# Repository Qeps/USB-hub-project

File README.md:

# PCB Design
Four-layer PCB project expanding two USB ports from a computer into eight downstream ports.
Designed in KiCad, conceptually based on the CircuitDigest (Original project: https://circuitdigest.com/electronic-circuits/diy-hub-port-extender) project, but extended to support two independent USB hub controllers.

Base Project (CircuitDigest)
- Uses the GL850G USB 2.0 hub controller
- Expands one USB port into four downstream ports
- Powered directly from 5 V USB input
- The controller integrates internal 3.3 V and 1.8 V regulators, no external LDO required
- Basic passive components: resistors and decoupling capacitors
- USB-A connectors for downstream ports and one upstream connector
- Includes ESD protection (TVS diodes) for both upstream and downstream ports

Extended Version (this project)
- Two upstream USB inputs expanded to eight downstream ports (two hub controllers)
- Implemented on a 4-layer PCB for improved power and signal routing
- Thickened power traces for stable 5 V distribution across all ports
- Matched USB data line lengths to maintain signal integrity and timing
- Guard ring added around USB signal area to improve EMI and ESD immunity
- Independent hub sections sharing common 5 V supply and ground planes

KiCAD schematic:

KiCAD 3D board view:

# Prototype Board
This project is currently under development and PCBWay provided the prototype boards as part of a collaboration. The PCBs arrived with consistent manufacturing quality: clean routing, correct layer alignment, and accurate silkscreen. 

The ordering workflow was straightforward. Uploading the Gerber files and selecting the manufacturing parameters was clear enough that the whole process stayed focused on the technical aspects of the design.

Photo of the prototypes:

Having the boards early in the process accelerates testing and helps refine the next revision.
Here you can order your board: https://www.pcbway.com/

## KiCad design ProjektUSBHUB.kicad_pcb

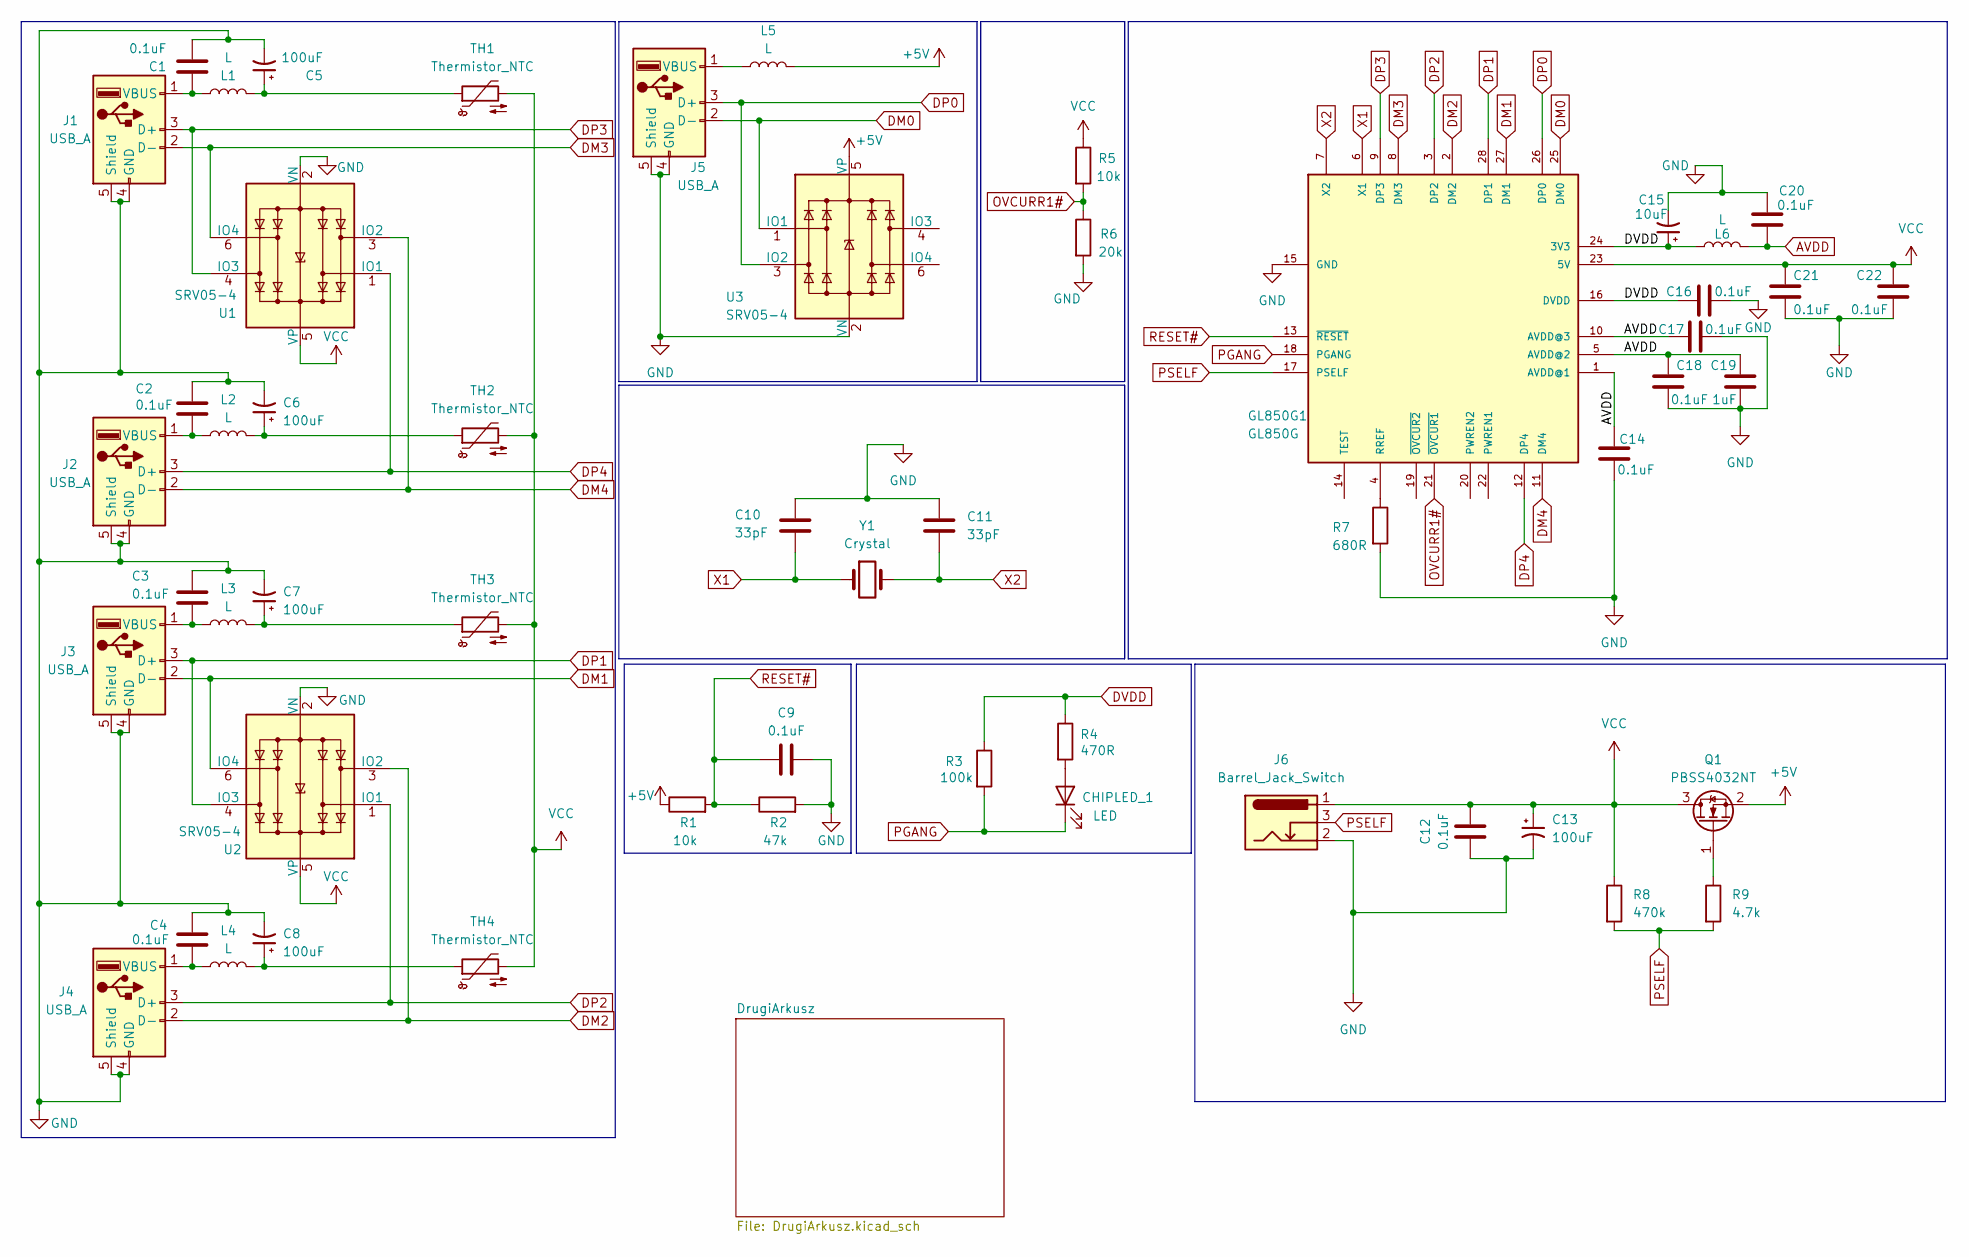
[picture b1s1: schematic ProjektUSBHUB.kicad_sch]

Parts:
C1, C2, C3, C4, C9, C12, C14, C16, C17, C18, C20, C21, C22: 0.1uF; C_0603_1608Metric_Pad1.08x0.95mm_HandSolder
C5, C6, C7, C8, C13: 100uF; C_Radial_D6.3mm_H11.0mm_P2.50mm
C10, C11: 33pF; C_0603_1608Metric_Pad1.08x0.95mm_HandSolder
C15: 10uF; C_Radial_D6.3mm_H11.0mm_P2.50mm
C19: 1uF; C_0603_1608Metric_Pad1.08x0.95mm_HandSolder
CHIPLED_1: LED; D_0805_2012Metric_Pad1.15x1.40mm_HandSolder
GL850G1: GL850G; SSOP28_GL850G_GEN-L
J1, J2, J3, J4, J5: USB_A; USB_A_TE_292303-7_Horizontal
J6: Barrel_Jack_Switch; PJ-102AH
L1, L2, L3, L4, L5, L6: L; L_0603_1608Metric_Pad1.05x0.95mm_HandSolder
Q1: PBSS4032NT; SOT-23
R1, R5: 10k; R_0603_1608Metric_Pad0.98x0.95mm_HandSolder
R2: 47k; R_0603_1608Metric_Pad0.98x0.95mm_HandSolder
R3: 100k; R_0603_1608Metric_Pad0.98x0.95mm_HandSolder
R4: 470R; R_0603_1608Metric_Pad0.98x0.95mm_HandSolder
R6: 20k; R_0603_1608Metric_Pad0.98x0.95mm_HandSolder
R7: 680R; R_0603_1608Metric_Pad0.98x0.95mm_HandSolder
R8: 470k; R_0603_1608Metric_Pad0.98x0.95mm_HandSolder
R9: 4.7k; R_0603_1608Metric_Pad0.98x0.95mm_HandSolder
TH1, TH2, TH3, TH4: Thermistor_NTC; R_0805_2012Metric_Pad1.20x1.40mm_HandSolder
U1, U2, U3: SRV05-4; TSOT-23-6_HandSoldering
Y1: Crystal; Crystal_SMD_ECS_CSM3X-2Pin_7.6x4.1mm

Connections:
+5V: L5.2, Q1.2 (S), R1.1, U3.5 (VP); also elsewhere on the board
AVDD: C14.1, C17.1, C18.1, C19.1, C20.2, GL850G1.1 (AVDD@1), GL850G1.5 (AVDD@2), GL850G1.10 (AVDD@3), L6.2
DM0: GL850G1.25 (DM0), J5.2 (D-), U3.1 (IO1)
DM1: GL850G1.27 (DM1), J3.2 (D-), U2.6 (IO4)
DM2: GL850G1.2 (DM2), J4.2 (D-), U2.3 (IO2)
DM3: GL850G1.8 (DM3), J1.2 (D-), U1.6 (IO4)
DM4: GL850G1.11 (DM4), J2.2 (D-), U1.3 (IO2)
DP0: GL850G1.26 (DP0), J5.3 (D+), U3.3 (IO2)
DP1: GL850G1.28 (DP1), J3.3 (D+), U2.4 (IO3)
DP2: GL850G1.3 (DP2), J4.3 (D+), U2.1 (IO1)
DP3: GL850G1.9 (DP3), J1.3 (D+), U1.4 (IO3)
DP4: GL850G1.12 (DP4), J2.3 (D+), U1.1 (IO1)
DVDD: C15.1, C16.1, GL850G1.16 (DVDD), GL850G1.24 (3V3), L6.1, R3.1, R4.1
GND: C1.2, C2.1, C3.1, C4.1, C5.2, C6.2, C7.2, C8.2, C9.2, C10.1, C11.1, C12.1, C13.2, C14.2, C15.2, C16.2, C17.2, C18.2, C19.2, C20.1, C21.2, C22.2, GL850G1.15 (GND), J1.4 (GND), J1.5 (Shield), J2.4 (GND), J2.5 (Shield), J3.4 (GND), J3.5 (Shield), J4.4 (GND), J4.5 (Shield), J5.4 (GND), J5.5 (Shield), J6.2, R2.2, R6.2, R7.2, U1.2 (VN), U2.2 (VN), U3.2 (VN); also elsewhere on the board
unnamed: C5.1, L1.2, TH1.1
unnamed: C6.1, L2.2, TH2.1
unnamed: C7.1, L3.2, TH3.1
unnamed: C8.1, L4.2, TH4.1
unnamed: CHIPLED_1.2 (A), R4.2
unnamed: GL850G1.4 (RREF), R7.1
unnamed: C1.1, J1.1 (VBUS), L1.1
unnamed: C2.2, J2.1 (VBUS), L2.1
unnamed: C3.2, J3.1 (VBUS), L3.1
unnamed: C4.2, J4.1 (VBUS), L4.1
unnamed: J5.1 (VBUS), L5.1
unnamed: Q1.1 (G), R9.1
OVCURR1#: GL850G1.21 (~OVCUR1), R5.2, R6.1
PGANG: CHIPLED_1.1 (K), GL850G1.18 (PGANG), R3.2
PSELF: GL850G1.17 (PSELF), J6.3, R8.2, R9.2; also elsewhere on the board
RESET#: C9.1, GL850G1.13 (~RESET), R1.2, R2.1
VCC: C12.2, C13.1, C21.1, C22.1, GL850G1.23 (5V), J6.1, Q1.3 (D), R5.1, R8.1, TH1.2, TH2.2, TH3.2, TH4.2, U1.5 (VP), U2.5 (VP); also elsewhere on the board
X1: C10.2, GL850G1.6 (X1), Y1.1
X2: C11.2, GL850G1.7 (X2), Y1.2

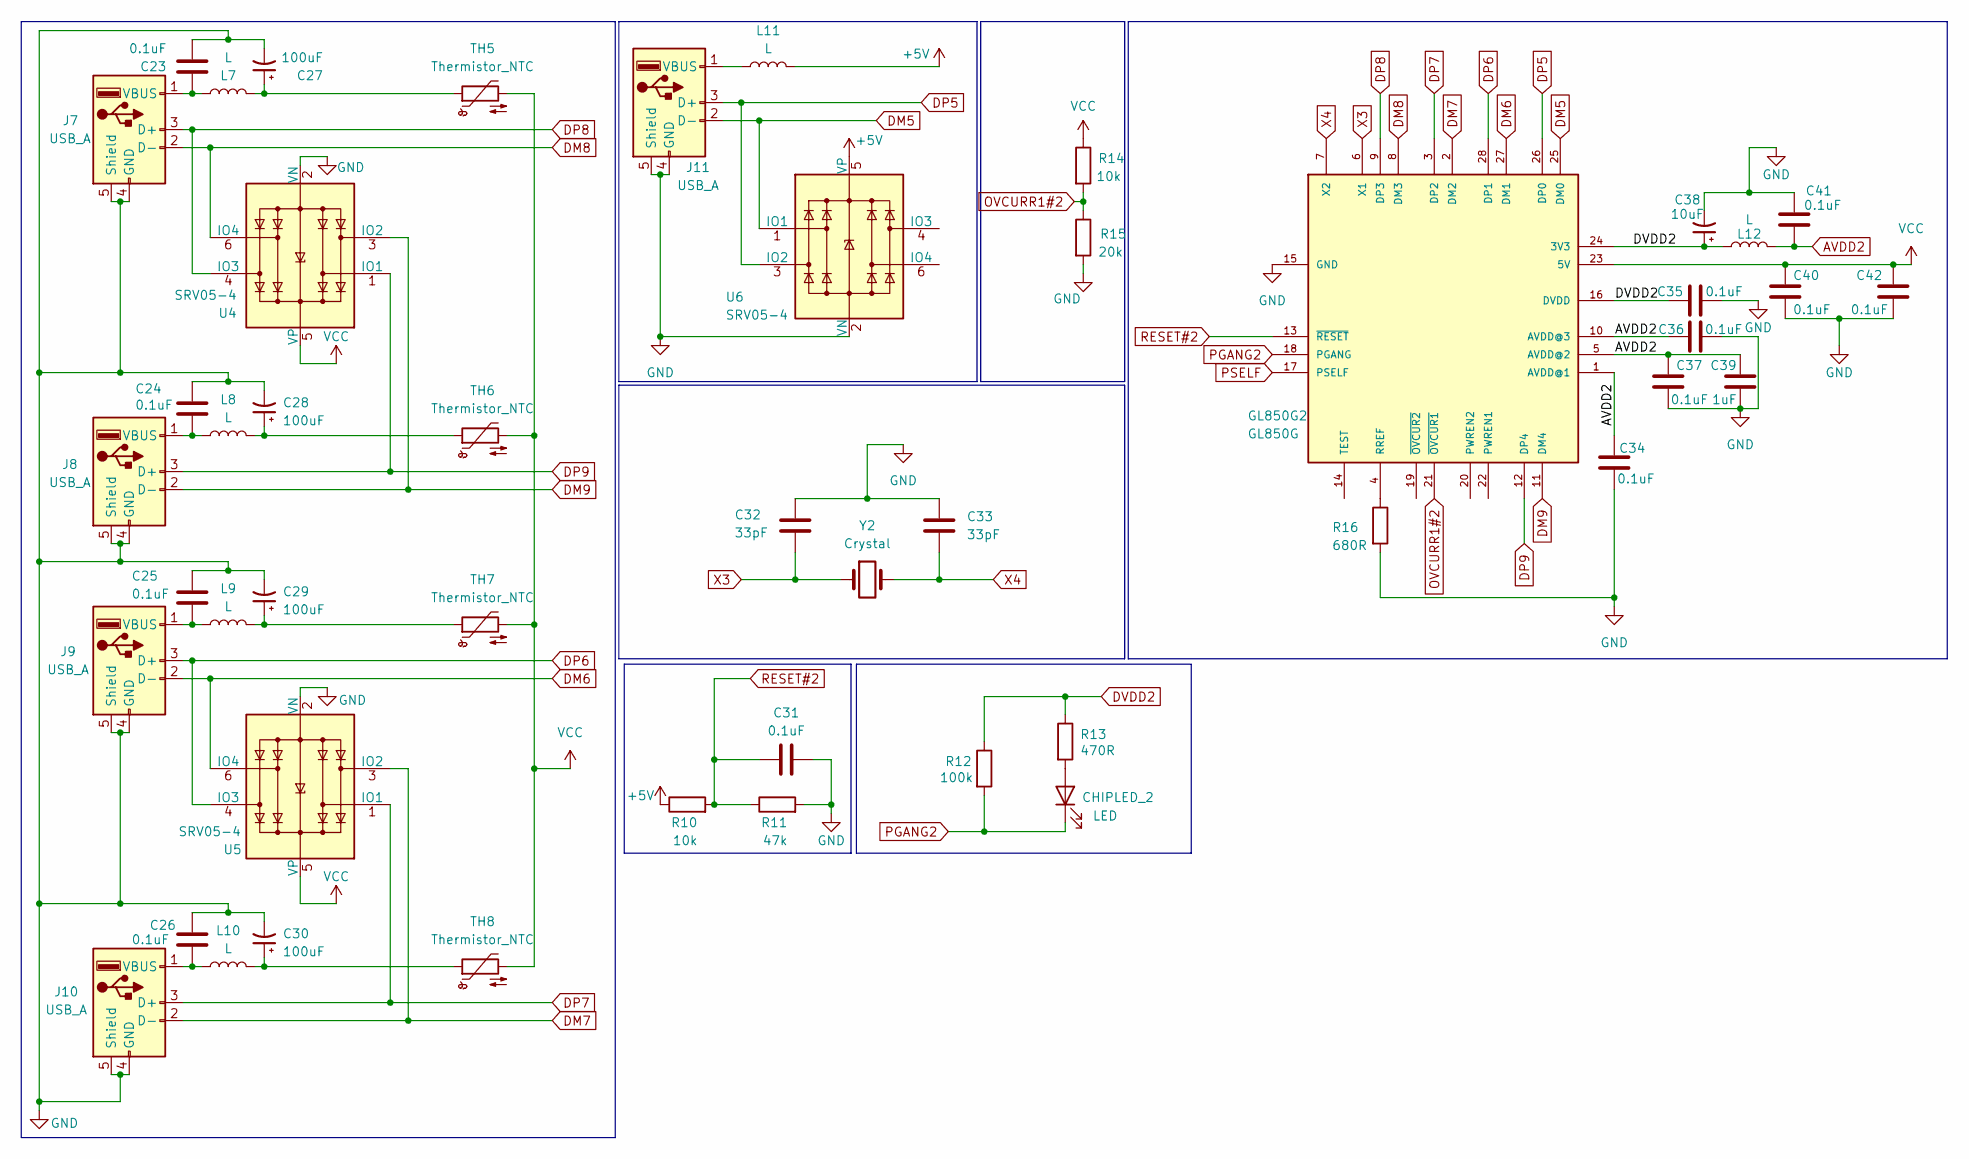
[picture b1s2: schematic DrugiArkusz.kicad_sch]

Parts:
C23, C24, C25, C26, C31, C34, C35, C36, C37, C40, C41, C42: 0.1uF; C_0603_1608Metric_Pad1.08x0.95mm_HandSolder
C27, C28, C29, C30: 100uF; C_Radial_D6.3mm_H11.0mm_P2.50mm
C32, C33: 33pF; C_0603_1608Metric_Pad1.08x0.95mm_HandSolder
C38: 10uF; C_Radial_D6.3mm_H11.0mm_P2.50mm
C39: 1uF; C_0603_1608Metric_Pad1.08x0.95mm_HandSolder
CHIPLED_2: LED; D_0805_2012Metric_Pad1.15x1.40mm_HandSolder
GL850G2: GL850G; SSOP28_GL850G_GEN-L
J7, J8, J9, J10, J11: USB_A; USB_A_TE_292303-7_Horizontal
L7, L8, L9, L10, L11, L12: L; L_0603_1608Metric_Pad1.05x0.95mm_HandSolder
R10, R14: 10k; R_0603_1608Metric_Pad0.98x0.95mm_HandSolder
R11: 47k; R_0603_1608Metric_Pad0.98x0.95mm_HandSolder
R12: 100k; R_0603_1608Metric_Pad0.98x0.95mm_HandSolder
R13: 470R; R_0603_1608Metric_Pad0.98x0.95mm_HandSolder
R15: 20k; R_0603_1608Metric_Pad0.98x0.95mm_HandSolder
R16: 680R; R_0603_1608Metric_Pad0.98x0.95mm_HandSolder
TH5, TH6, TH7, TH8: Thermistor_NTC; R_0805_2012Metric_Pad1.20x1.40mm_HandSolder
U4, U5, U6: SRV05-4; TSOT-23-6_HandSoldering
Y2: Crystal; Crystal_SMD_ECS_CSM3X-2Pin_7.6x4.1mm

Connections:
+5V: L11.2, R10.1, U6.5 (VP); also elsewhere on the board
AVDD2: C34.1, C36.1, C37.1, C39.1, C41.2, GL850G2.1 (AVDD@1), GL850G2.5 (AVDD@2), GL850G2.10 (AVDD@3), L12.2
DM5: GL850G2.25 (DM0), J11.2 (D-), U6.1 (IO1)
DM6: GL850G2.27 (DM1), J9.2 (D-), U5.6 (IO4)
DM7: GL850G2.2 (DM2), J10.2 (D-), U5.3 (IO2)
DM8: GL850G2.8 (DM3), J7.2 (D-), U4.6 (IO4)
DM9: GL850G2.11 (DM4), J8.2 (D-), U4.3 (IO2)
DP5: GL850G2.26 (DP0), J11.3 (D+), U6.3 (IO2)
DP6: GL850G2.28 (DP1), J9.3 (D+), U5.4 (IO3)
DP7: GL850G2.3 (DP2), J10.3 (D+), U5.1 (IO1)
DP8: GL850G2.9 (DP3), J7.3 (D+), U4.4 (IO3)
DP9: GL850G2.12 (DP4), J8.3 (D+), U4.1 (IO1)
DVDD2: C35.1, C38.1, GL850G2.16 (DVDD), GL850G2.24 (3V3), L12.1, R12.1, R13.1
GND: C23.2, C24.1, C25.1, C26.1, C27.2, C28.2, C29.2, C30.2, C31.2, C32.1, C33.1, C34.2, C35.2, C36.2, C37.2, C38.2, C39.2, C40.2, C41.1, C42.2, GL850G2.15 (GND), J7.4 (GND), J7.5 (Shield), J8.4 (GND), J8.5 (Shield), J9.4 (GND), J9.5 (Shield), J10.4 (GND), J10.5 (Shield), J11.4 (GND), J11.5 (Shield), R11.2, R15.2, R16.2, U4.2 (VN), U5.2 (VN), U6.2 (VN); also elsewhere on the board
unnamed: C27.1, L7.2, TH5.1
unnamed: C28.1, L8.2, TH6.1
unnamed: C29.1, L9.2, TH7.1
unnamed: C30.1, L10.2, TH8.1
unnamed: CHIPLED_2.2 (A), R13.2
unnamed: GL850G2.4 (RREF), R16.1
unnamed: C23.1, J7.1 (VBUS), L7.1
unnamed: C24.2, J8.1 (VBUS), L8.1
unnamed: C25.2, J9.1 (VBUS), L9.1
unnamed: C26.2, J10.1 (VBUS), L10.1
unnamed: J11.1 (VBUS), L11.1
OVCURR1#2: GL850G2.21 (~OVCUR1), R14.2, R15.1
PGANG2: CHIPLED_2.1 (K), GL850G2.18 (PGANG), R12.2
PSELF: GL850G2.17 (PSELF); also elsewhere on the board
RESET#2: C31.1, GL850G2.13 (~RESET), R10.2, R11.1
VCC: C40.1, C42.1, GL850G2.23 (5V), R14.1, TH5.2, TH6.2, TH7.2, TH8.2, U4.5 (VP), U5.5 (VP); also elsewhere on the board
X3: C32.2, GL850G2.6 (X1), Y2.1
X4: C33.2, GL850G2.7 (X2), Y2.2

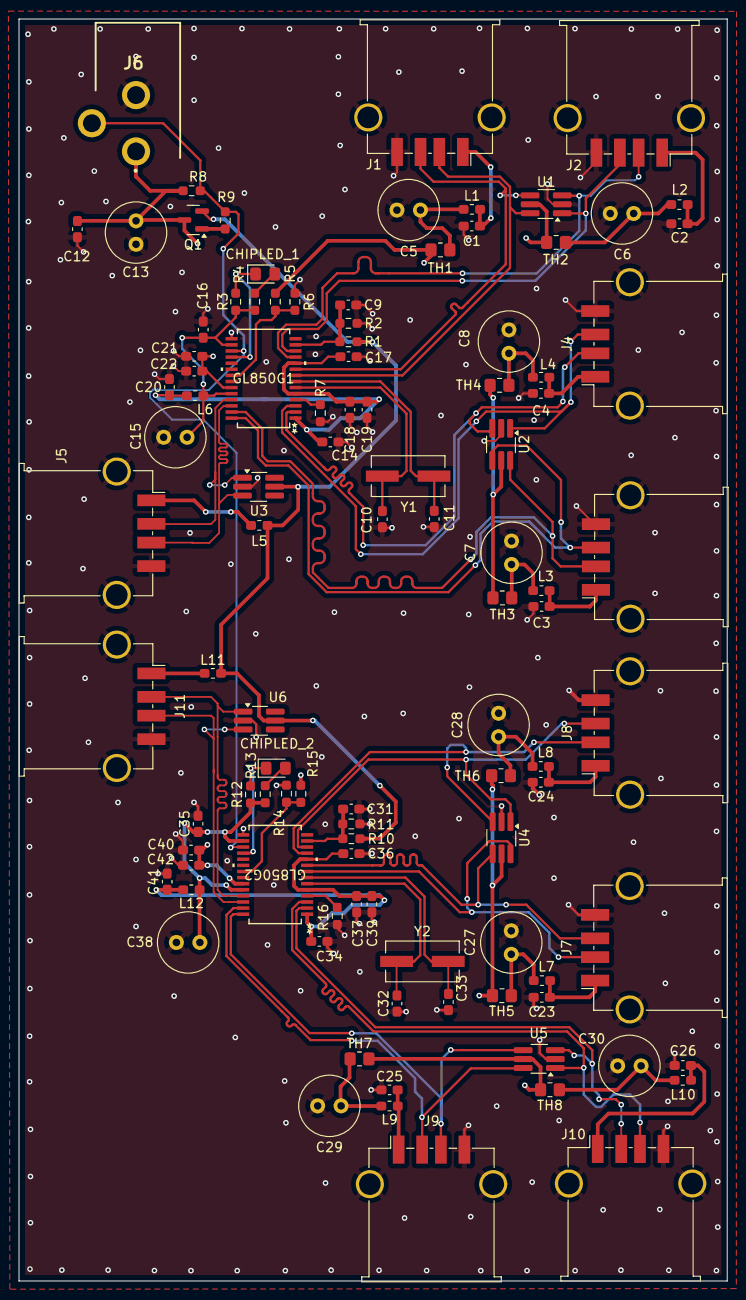
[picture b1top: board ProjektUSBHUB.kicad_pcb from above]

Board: 4 copper layers, 75.4 x 134.4 mm, 102 parts (0 on the bottom side), 61 nets.

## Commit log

2025-10-09 PCB design
2025-11-21 Update README.md
    Added a section about the prototype board development and collaboration with PCBWay.
2025-11-21 Update README.md
    Added ordering link for the board.
